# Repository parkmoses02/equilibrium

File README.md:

# equilibrium
Double Inverted Pendulum Control - 6인 팀 프로젝트  이중 역진자 시스템의 동역학 모델링과 제어 알고리즘 구현을 위한 공동 개발 저장소입니다.

프로젝트 목표:
- 정확한 비선형/선형화 모델 개발
- 다양한 제어 기법(LQR, PID, MPC 등) 비교 및 적용
- 시뮬레이션 환경 구축 및 성능 분석
- 코드 품질과 문서화 유지

로컬 환경 구성 안내:
- [LOCAL_SETUP.md](LOCAL_SETUP.md)

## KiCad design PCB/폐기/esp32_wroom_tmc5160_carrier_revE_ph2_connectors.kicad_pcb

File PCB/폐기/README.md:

# Freenove ESP32 WROOM + TMC5160T Pro Carrier Rev.C Routed

Two-layer routed carrier reconstructed from the supplied images.

## Mechanical assumptions

- PCB: 100 x 80 mm, four M3 holes
- ESP32 WROOM headers: 2.54 mm pitch, 20 pins per side, assumed 27.94 mm row spacing
- TMC5160T Pro: 2.54 mm pitch, assumed 15.24 mm row spacing

## Routing rules applied

- VMOT: 2.00 mm
- Motor phases A1/A2/B1/B2: 1.50 mm
- +5V: 1.00 mm
- +3V3: 0.50 mm
- Digital and encoder signals: 0.30 mm
- Ground zones: F.Cu and B.Cu
- Encoder: 4.7k pull-ups to 3.3 V and 100-ohm series resistors

## Before fabrication

GPIO16 and GPIO17 are left unconnected. Press B in KiCad to refill zones and run DRC. Confirm both module footprints and every connector orientation with a 1:1 paper print and the real hardware before ordering.

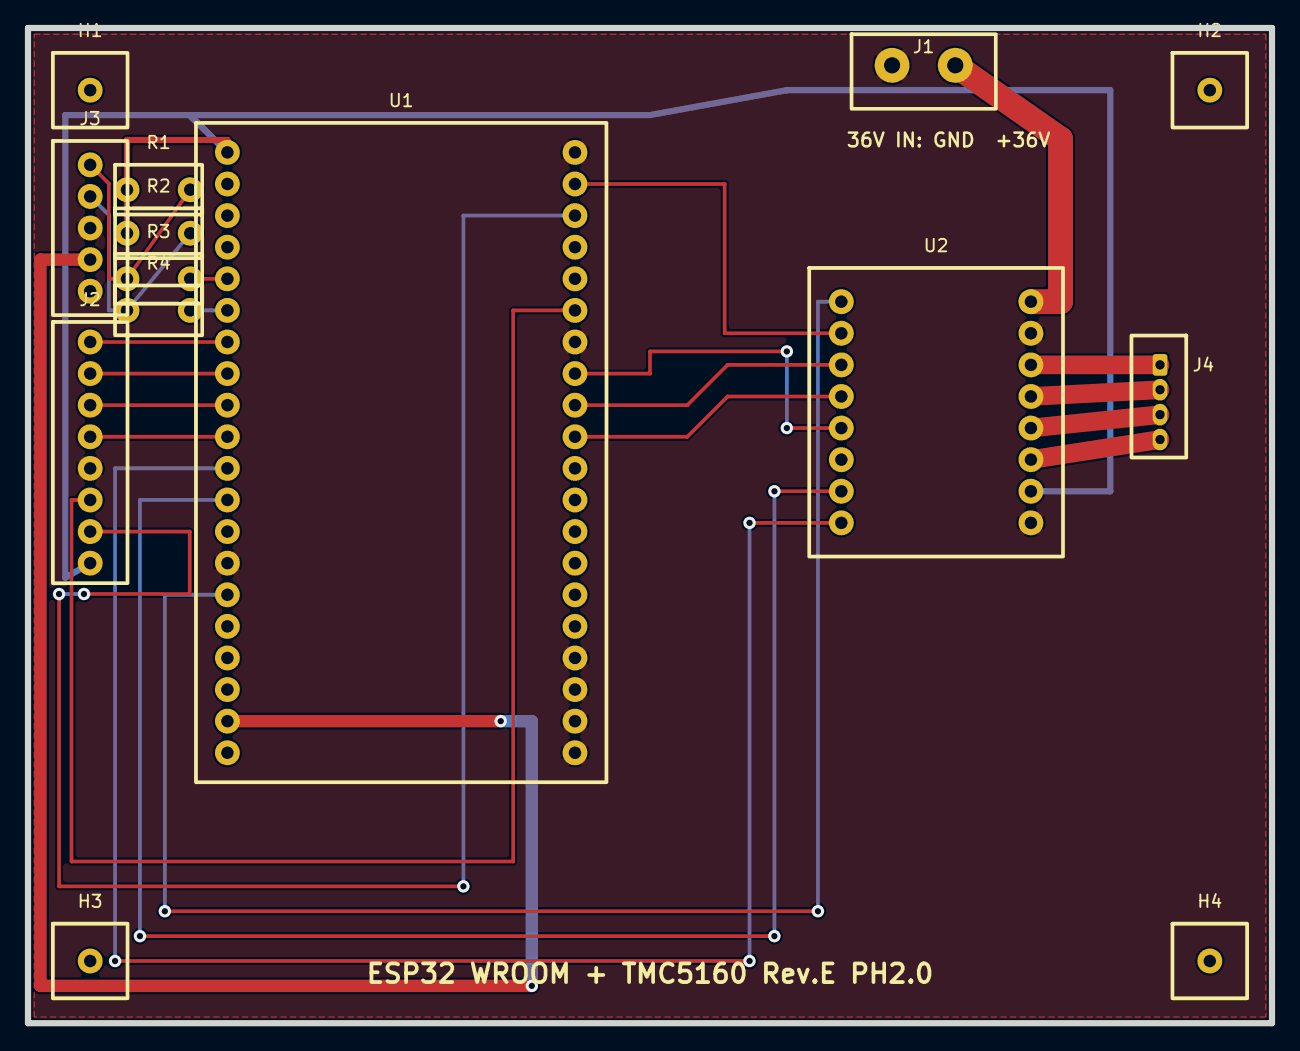
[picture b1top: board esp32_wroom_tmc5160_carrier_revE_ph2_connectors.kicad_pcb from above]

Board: 2 copper layers, 100.0 x 80.0 mm, 14 parts (0 on the bottom side), 25 nets.

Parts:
H1, H2, H3, H4: M3_MOUNT
J1: 36V INPUT 2P 5.08mm TERMINAL; TERMINAL_BLOCK_2P_5.08
J2: SPARE GPIO / 1x8 2.54mm FEMALE SOCKET; IO_1x8_2.54_VERTICAL
J3: ENCODER / 1x5 2.54mm FEMALE SOCKET; ENCODER_1x5_2.54_VERTICAL
J4: JST-PH B4B-PH-K 4-pin 2.00mm MALE; JST_PH_B4B-PH-K_1x04_P2.00mm_Vertical
R1: R_A_PULLUP_4K7
R2: R_B_PULLUP_4K7
R3: R_A_SERIES_100R
R4: R_B_SERIES_100R
U1: FREENOVE ESP32 WROOM / 1x20 2.54mm FEMALE SOCKET 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; FREENOVE_ESP32_WROOM_2x20
U2: TMC5160T PRO / 1x8 2.54mm FEMALE SOCKET x2; TMC5160T_PRO_2x8

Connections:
+3V3: J2.8, R1.1, R2.1, U1.L1, U2.15
+5V: J3.4, U1.L19
ENC_A: R3.2, U1.L5
ENC_A_RAW: J3.1, R1.2, R3.1
ENC_B: R4.2, U1.L6
ENC_B_RAW: J3.2, R2.2, R4.1
GND: J1.1, J2.5, J3.3, J3.5, U1.L14, U1.R1, U1.R7, U1.R17, U1.R18, U1.R19, U1.R20, U2.10, U2.16
IO21: J2.6, U1.R6
IO22: J2.7, U1.R3
IO25: J2.3, U1.L9
IO26: J2.4, U1.L10
IO32: J2.1, U1.L7
IO33: J2.2, U1.L8
M_A1: J4.2, U2.12
M_A2: J4.1, U2.11
M_B1: J4.4, U2.14
M_B2: J4.3, U2.13
SPI_CS: U1.R10, U2.4
SPI_MISO: U1.R8, U2.5
SPI_MOSI: U1.R2, U2.2
SPI_SCK: U1.R9, U2.3
TMC_DIR: U1.L11, U2.8
TMC_EN: U1.L15, U2.1
TMC_STEP: U1.L12, U2.7
VMOT: J1.2, U2.9

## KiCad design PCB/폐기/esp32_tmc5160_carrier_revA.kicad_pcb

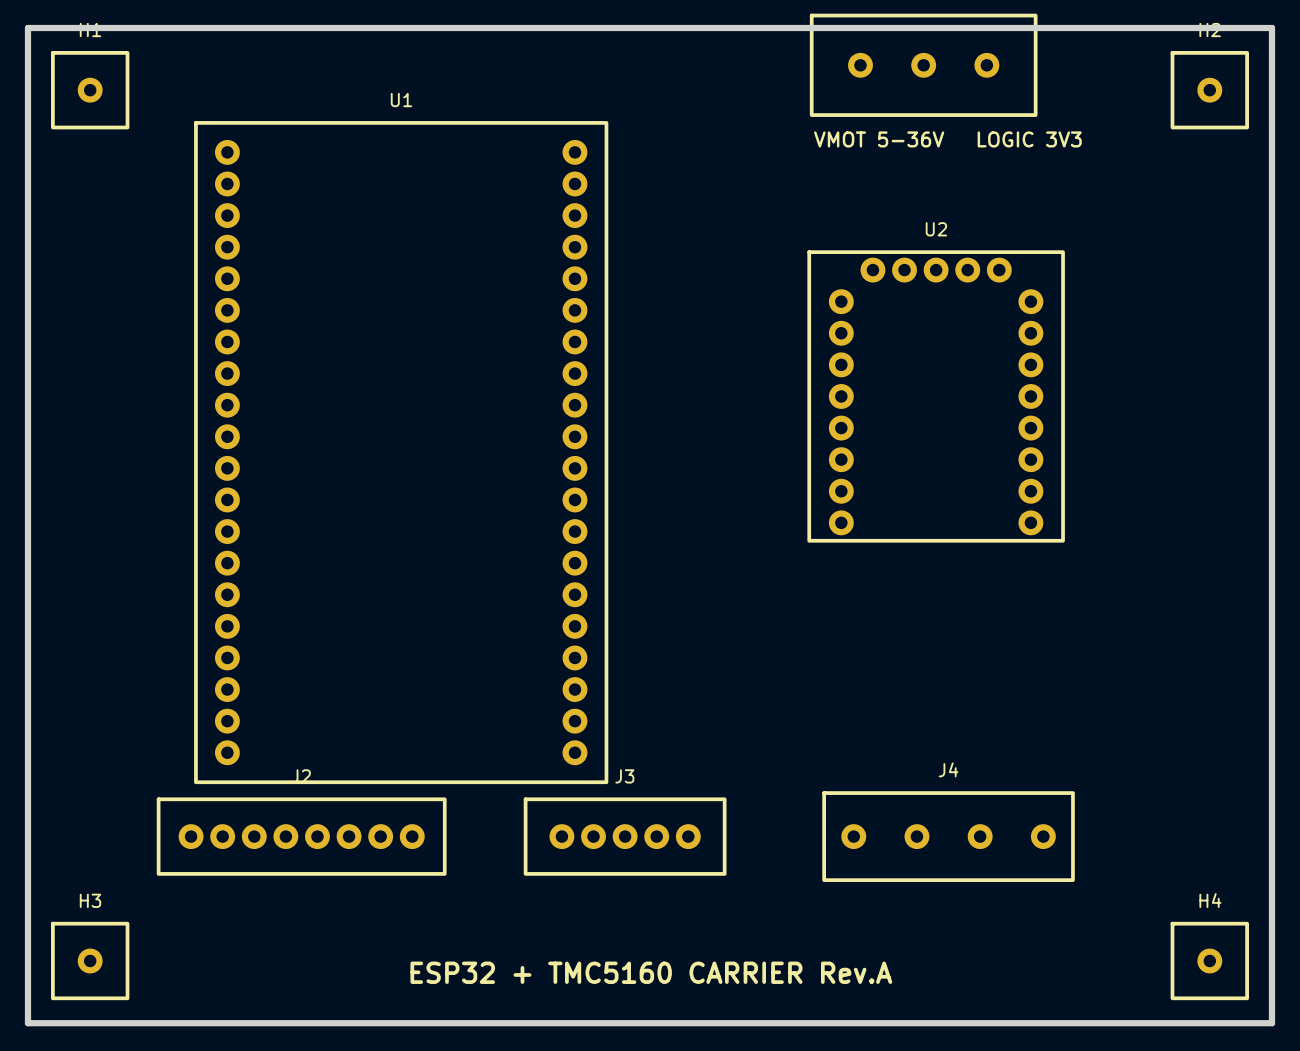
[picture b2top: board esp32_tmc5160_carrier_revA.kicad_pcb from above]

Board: 2 copper layers, 100.0 x 80.0 mm, 10 parts (0 on the bottom side), 24 nets, no tracks yet.

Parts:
H1, H2, H3, H4: M3_MOUNT
J1: POWER_VMOT_3P_5.08
J2: IO_1x8_2.54
J3: ENCODER_1x5_2.54
J4: MOTOR_1x4_5.08
U1: FREENOVE_ESP32_WROVER_CAM_2x20
U2: TMC5160T_PRO_2x8

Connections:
+3V3: J2.8, U1.L1, U2.15
+5V: J1.2, J3.4, U1.L19
ENC_A: J3.2, U2.20
ENC_B: J3.1, U2.19
ENC_N: J3.5, U2.21
GND: J1.1, J2.1, J3.3, U1.L14, U1.R1, U1.R7, U1.R11, U1.R12, U1.R20, U2.10, U2.16
IO21: J2.2, U1.R6
IO22: J2.3, U1.R3
IO25: J2.4, U1.L9
IO26: J2.5, U1.L10
IO32: J2.6, U1.L7
IO33: J2.7, U1.L8
M_A1: J4.1, U2.12
M_A2: J4.2, U2.11
M_B1: J4.3, U2.14
M_B2: J4.4, U2.13
SPI_CS: U1.R10, U2.4
SPI_MISO: U1.R8, U2.5
SPI_MOSI: U1.R2, U2.2
SPI_SCK: U1.R9, U2.3
TMC_DIR: U1.L11, U2.8
TMC_EN: U1.L15, U2.1
TMC_STEP: U1.L12, U2.7
VMOT: J1.3, U2.9

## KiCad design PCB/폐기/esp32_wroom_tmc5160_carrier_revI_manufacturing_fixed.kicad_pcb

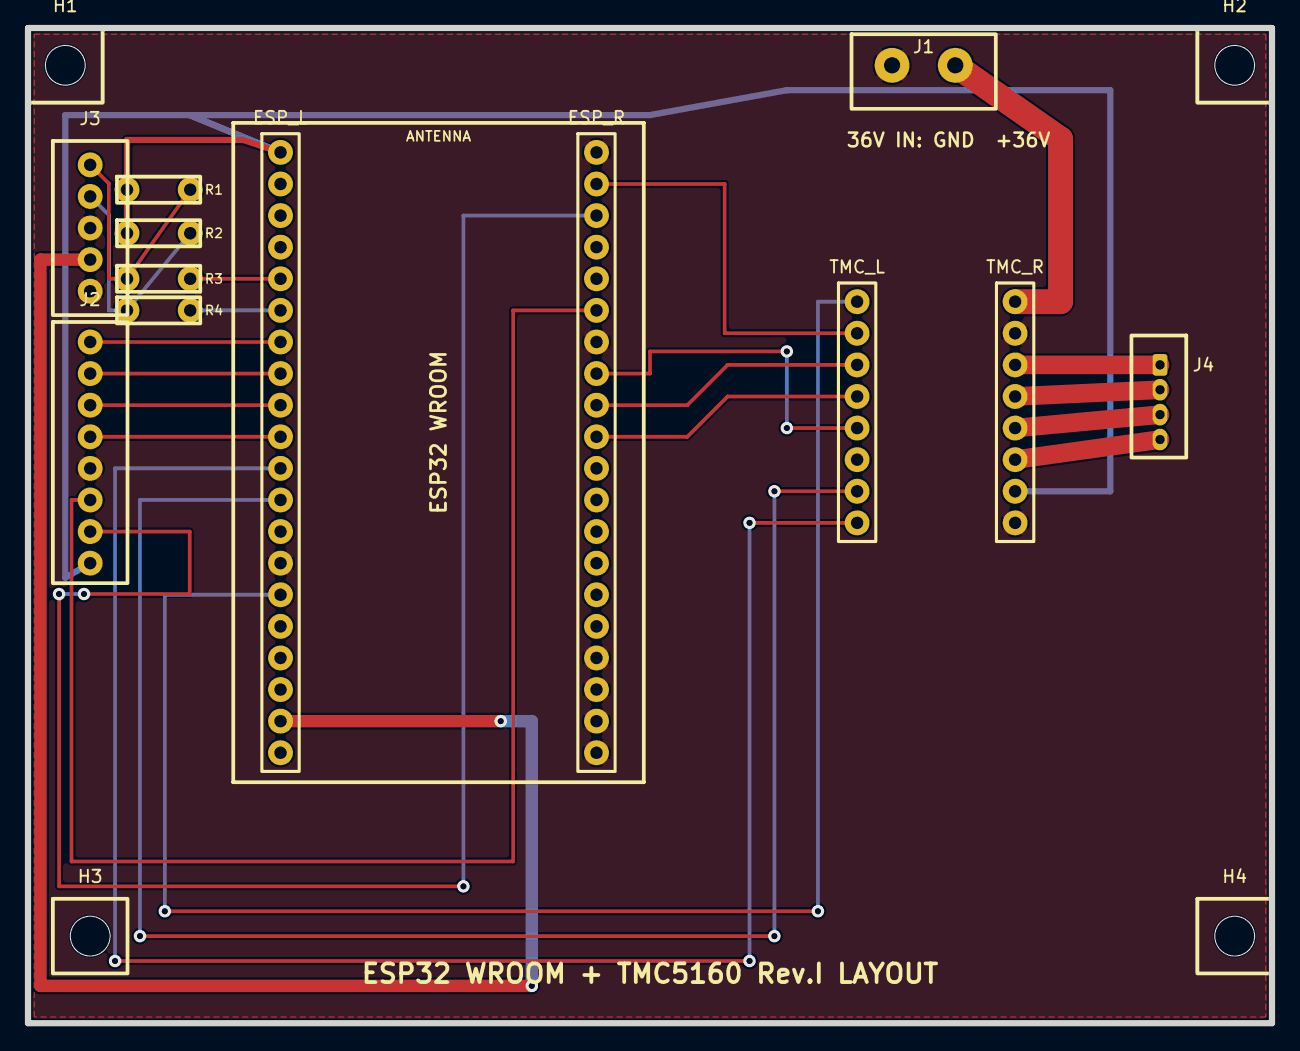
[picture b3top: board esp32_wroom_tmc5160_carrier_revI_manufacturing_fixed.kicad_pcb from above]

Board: 2 copper layers, 100.0 x 80.0 mm, 16 parts (0 on the bottom side), 25 nets.

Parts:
ESP_L: 1x20 2.54mm FEMALE SOCKET; ESP_L_1x20_PCBA
ESP_R: 1x20 2.54mm FEMALE SOCKET; ESP_R_1x20_PCBA
H1, H2, H3, H4: M3_MOUNT
J1: 36V INPUT 2P 5.08mm TERMINAL; TERMINAL_BLOCK_2P_5.08
J2: SPARE GPIO / 1x8 2.54mm FEMALE SOCKET; IO_1x8_2.54_VERTICAL
J3: ENCODER / 1x5 2.54mm FEMALE SOCKET; ENCODER_1x5_2.54_VERTICAL
J4: JST-PH B4B-PH-K 4-pin 2.00mm MALE; JST_PH_B4B-PH-K_1x04_P2.00mm_Vertical
R1: R_A_PULLUP_4K7
R2: R_B_PULLUP_4K7
R3: R_A_SERIES_100R
R4: R_B_SERIES_100R
TMC_L: 1x8 2.54mm FEMALE SOCKET; TMC_L_1x08_PCBA
TMC_R: 1x8 2.54mm FEMALE SOCKET; TMC_R_1x08_PCBA

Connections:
+3V3: ESP_L.L1, J2.8, R1.1, R2.1, TMC_R.15
+5V: ESP_L.L19, J3.4
ENC_A: ESP_L.L5, R3.2
ENC_A_RAW: J3.1, R1.2, R3.1
ENC_B: ESP_L.L6, R4.2
ENC_B_RAW: J3.2, R2.2, R4.1
GND: ESP_L.L14, ESP_R.R1, ESP_R.R7, ESP_R.R17, ESP_R.R18, ESP_R.R19, ESP_R.R20, J1.1, J2.5, J3.3, J3.5, TMC_R.10, TMC_R.16
IO21: ESP_R.R6, J2.6
IO22: ESP_R.R3, J2.7
IO25: ESP_L.L9, J2.3
IO26: ESP_L.L10, J2.4
IO32: ESP_L.L7, J2.1
IO33: ESP_L.L8, J2.2
M_A1: J4.2, TMC_R.12
M_A2: J4.1, TMC_R.11
M_B1: J4.4, TMC_R.14
M_B2: J4.3, TMC_R.13
SPI_CS: ESP_R.R10, TMC_L.4
SPI_MISO: ESP_R.R8, TMC_L.5
SPI_MOSI: ESP_R.R2, TMC_L.2
SPI_SCK: ESP_R.R9, TMC_L.3
TMC_DIR: ESP_L.L11, TMC_L.8
TMC_EN: ESP_L.L15, TMC_L.1
TMC_STEP: ESP_L.L12, TMC_L.7
VMOT: J1.2, TMC_R.9

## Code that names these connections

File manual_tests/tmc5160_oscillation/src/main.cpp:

#include <Arduino.h>
#include <SPI.h>

// ESP32 WROOM + carrier Rev.J pin map.
constexpr uint8_t PIN_TMC_EN   = 13;  // Active LOW
constexpr uint8_t PIN_TMC_STEP = 14;
constexpr uint8_t PIN_TMC_DIR  = 27;
constexpr uint8_t PIN_TMC_CS   = 5;
constexpr uint8_t PIN_SPI_MISO = 19;
constexpr uint8_t PIN_SPI_MOSI = 23;
constexpr uint8_t PIN_SPI_SCK  = 18;

// Conservative first-test motion: 200 microsteps/s for one second.
constexpr uint32_t MOVE_TIME_MS = 1000;
constexpr uint32_t PAUSE_TIME_MS = 1000;
constexpr uint32_t STEP_HALF_PERIOD_US = 2500;

constexpr uint8_t REG_GCONF        = 0x00;
constexpr uint8_t REG_IOIN         = 0x04;
constexpr uint8_t REG_GLOBALSCALER = 0x0B;
constexpr uint8_t REG_IHOLD_IRUN   = 0x10;
constexpr uint8_t REG_TPOWERDOWN   = 0x11;
constexpr uint8_t REG_CHOPCONF     = 0x6C;
constexpr uint8_t WRITE_FLAG       = 0x80;

SPISettings tmcSpi(1000000, MSBFIRST, SPI_MODE3);

void writeRegister(uint8_t address, uint32_t value) {
  SPI.beginTransaction(tmcSpi);
  digitalWrite(PIN_TMC_CS, LOW);
  SPI.transfer(address | WRITE_FLAG);
  SPI.transfer(static_cast<uint8_t>(value >> 24));
  SPI.transfer(static_cast<uint8_t>(value >> 16));
  SPI.transfer(static_cast<uint8_t>(value >> 8));
  SPI.transfer(static_cast<uint8_t>(value));
  digitalWrite(PIN_TMC_CS, HIGH);
  SPI.endTransaction();
}

uint32_t readRegister(uint8_t address) {
  // TMC5160 returns the requested register on the following SPI transaction.
  for (uint8_t transaction = 0; transaction < 2; ++transaction) {
    SPI.beginTransaction(tmcSpi);
    digitalWrite(PIN_TMC_CS, LOW);
    SPI.transfer(address & 0x7F);
    SPI.transfer(0);
    SPI.transfer(0);
    SPI.transfer(0);
    SPI.transfer(0);
    digitalWrite(PIN_TMC_CS, HIGH);
    SPI.endTransaction();
  }

  SPI.beginTransaction(tmcSpi);
  digitalWrite(PIN_TMC_CS, LOW);
  SPI.transfer(address & 0x7F);
  uint32_t value = static_cast<uint32_t>(SPI.transfer(0)) << 24;
  value |= static_cast<uint32_t>(SPI.transfer(0)) << 16;
  value |= static_cast<uint32_t>(SPI.transfer(0)) << 8;
  value |= static_cast<uint32_t>(SPI.transfer(0));
  digitalWrite(PIN_TMC_CS, HIGH);
  SPI.endTransaction();
  return value;
}

[[noreturn]] void stopWithError(const char *message) {
  digitalWrite(PIN_TMC_EN, HIGH);
  Serial.println(message);
  Serial.println("Driver remains DISABLED. Remove VM power before checking wiring.");
  while (true) delay(1000);
}

void configureDriver() {
  // SpreadCycle, normal STEP/DIR operation.
  writeRegister(REG_GCONF, 0x00000000);

  // BTT TMC5160 V1.0 has 0.075 ohm sense resistors.
  // IHOLD=4, IRUN=8, IHOLDDELAY=6 and GLOBALSCALER=128 provide a
  // deliberately conservative first-test current (roughly 0.3-0.4 A RMS).
  writeRegister(REG_GLOBALSCALER, 128);
  writeRegister(REG_IHOLD_IRUN, (6UL << 16) | (8UL << 8) | 4UL);
  writeRegister(REG_TPOWERDOWN, 10);

  // 16 microsteps, TOFF=3, HSTRT=4, HEND=1, TBL=2.
  const uint32_t chopconf = (4UL << 24) | (2UL << 15) |
                            (1UL << 7) | (4UL << 4) | 3UL;
  writeRegister(REG_CHOPCONF, chopconf);
}

void moveForOneSecond(bool direction) {
  digitalWrite(PIN_TMC_DIR, direction ? HIGH : LOW);
  delayMicroseconds(20);

  const uint32_t deadline = millis() + MOVE_TIME_MS;
  while (static_cast<int32_t>(deadline - millis()) > 0) {
    digitalWrite(PIN_TMC_STEP, HIGH);
    delayMicroseconds(STEP_HALF_PERIOD_US);
    digitalWrite(PIN_TMC_STEP, LOW);
    delayMicroseconds(STEP_HALF_PERIOD_US);
  }
}

void setup() {
  pinMode(PIN_TMC_EN, OUTPUT);
  pinMode(PIN_TMC_STEP, OUTPUT);
  pinMode(PIN_TMC_DIR, OUTPUT);
  pinMode(PIN_TMC_CS, OUTPUT);

  // Keep the power stage disabled until communication and configuration pass.
  digitalWrite(PIN_TMC_EN, HIGH);
  digitalWrite(PIN_TMC_STEP, LOW);
  digitalWrite(PIN_TMC_DIR, LOW);
  digitalWrite(PIN_TMC_CS, HIGH);

  Serial.begin(115200);
  SPI.begin(PIN_SPI_SCK, PIN_SPI_MISO, PIN_SPI_MOSI, PIN_TMC_CS);

  Serial.println();
  Serial.println("TMC5160 cautious oscillation test");
  Serial.println("Motor must be unloaded; use 12 V VM and a heatsink.");
  Serial.println("Starting in 3 seconds...");
  delay(3000);

  const uint32_t ioin = readRegister(REG_IOIN);
  const uint8_t version = static_cast<uint8_t>(ioin >> 24);
  Serial.printf("IOIN=0x%08lX, VERSION=0x%02X\n", ioin, version);
  if (version != 0x30) {
    stopWithError("ERROR: TMC5160 SPI response is invalid.");
  }

  configureDriver();
  digitalWrite(PIN_TMC_EN, LOW);
  Serial.println("Driver enabled. Beginning 1 s left/right motion.");
}

void loop() {
  Serial.println("Direction A: 1 second");
  moveForOneSecond(false);
  delay(PAUSE_TIME_MS);

  Serial.println("Direction B: 1 second");
  moveForOneSecond(true);
  delay(PAUSE_TIME_MS);
}

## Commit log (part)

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2026-03-26 Format README for better readability
2026-04-03 아무거나
2026-04-03 test commit
2026-04-03 ㅇㄹㅇㄹㅇ
2026-04-03 test
2026-04-03 bin file and calculation code
2026-04-03 food
2026-04-03 test2
2026-04-03 setup
2026-04-03 템플릿 수정
2026-04-03 uv 사용법
2026-04-03 파일 정리
2026-04-04 vs code commit 설정
2026-04-24 시뮬레이션 프로그램 수정
2026-05-01 단진자 시뮬레이션 추가
2026-05-01 단일진자 업그레이드
2026-05-21 chore: remove orphaned pip package files and caches from virtual environment
2026-05-21 chore: initialize project with Python 3.13 and uv dependency management
2026-05-21 docs: update local setup guide to use uv for environment and dependency management
2026-05-21 chore: remove .vscode from version control
2026-05-21 separate LQR
2026-05-24 Replace magdi branch with current Balance_ESP32C3_1_1 workspace
2026-05-24 일단 업데이트
2026-05-25 시뮬구체화
